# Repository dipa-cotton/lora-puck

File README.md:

# lora-puck
LoRA!!
## pictures

## project overview
A long range radio system with lots of features! it integrates boards with sensors and reads the data with an esp32, and communicates using an SX1262, on ham radio frequencies so i can pick them up from far far away :DD along with a 0.96 inch OLED display, a microSD card module, and more, this project is versatile and can do much more than your average tiny radio!
## pictures
There was no CAD Case built because this is going to be put in a solar powered plane built by an organization that I don't have the dimentions for yet. I will update the CAD as soon as I receive those dimentions!
### Overall Cost: $72
see BOM.csv for more specifics!

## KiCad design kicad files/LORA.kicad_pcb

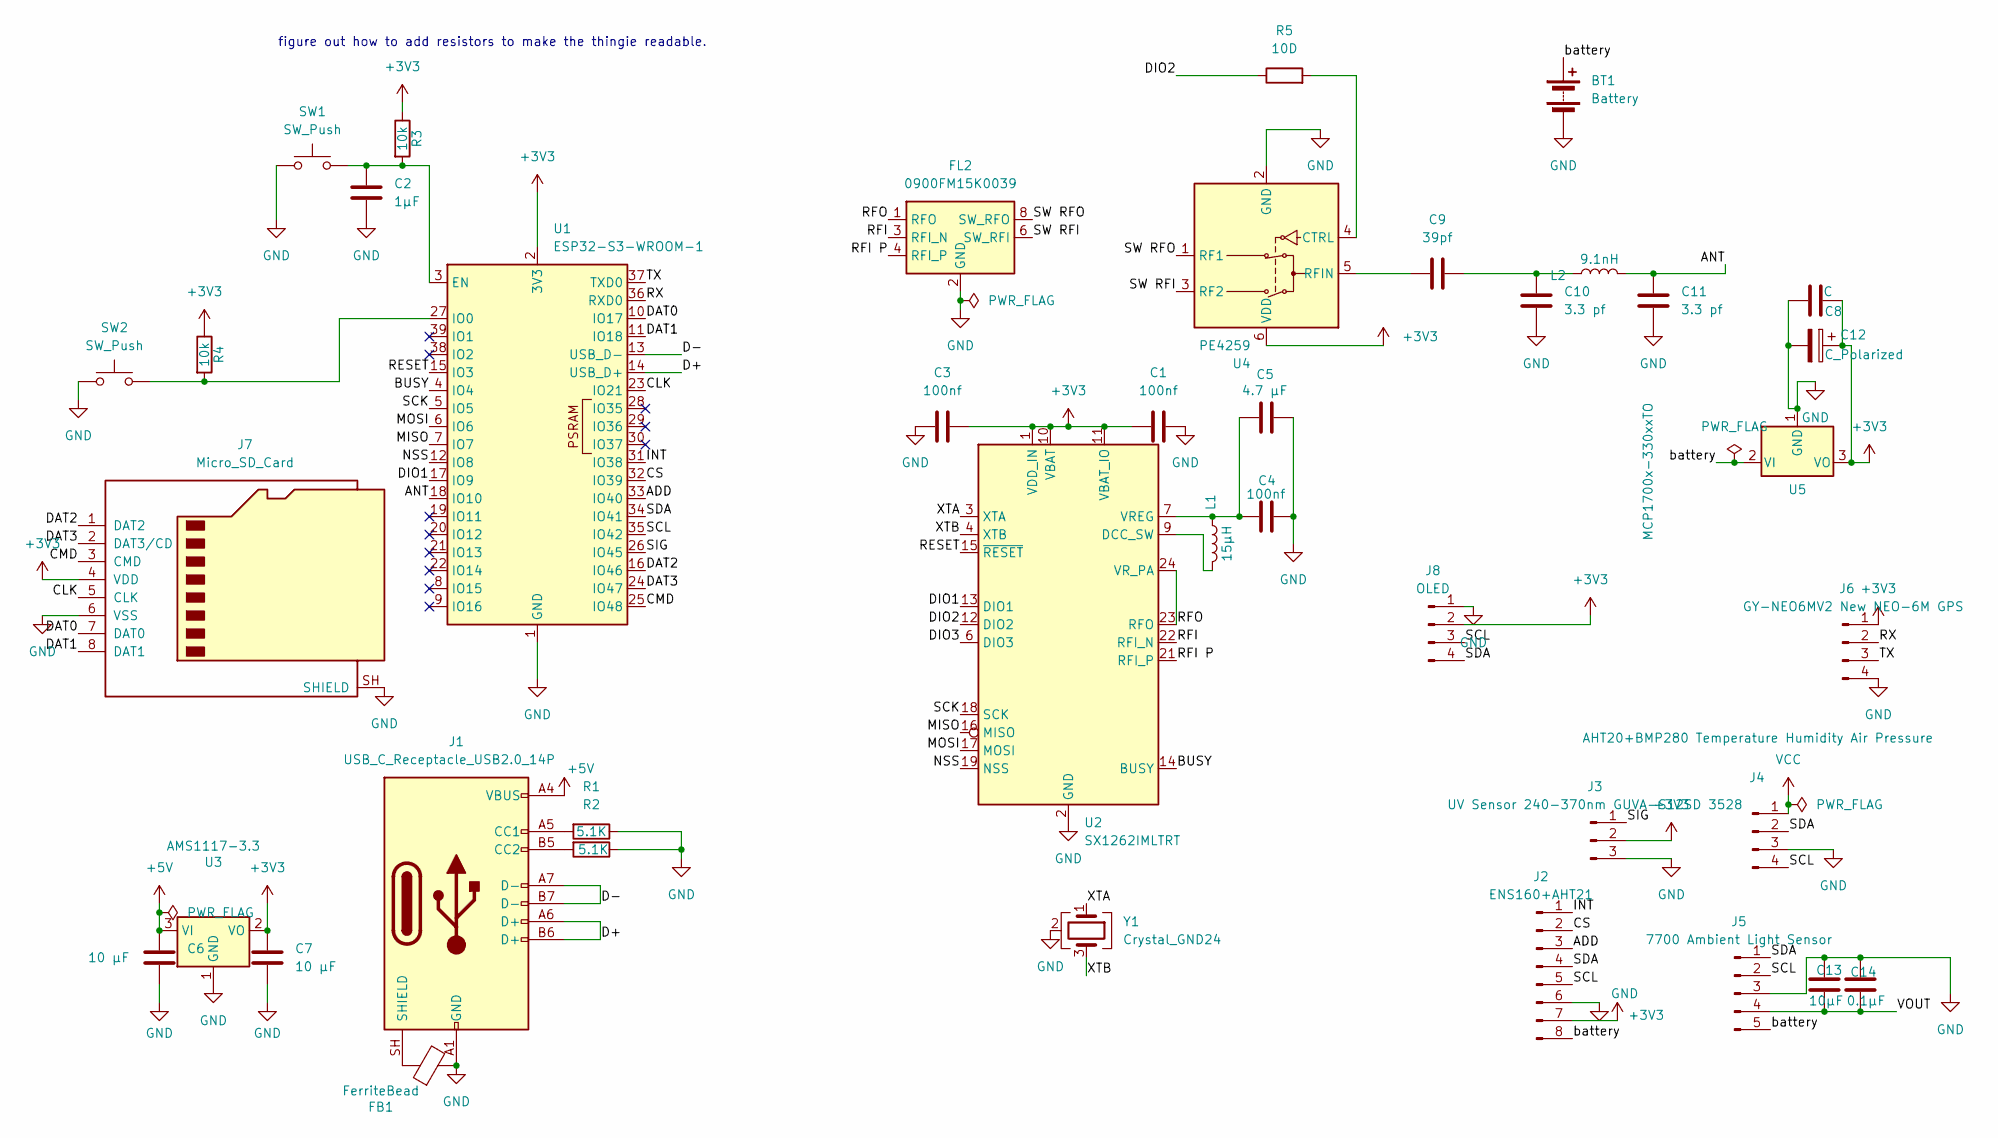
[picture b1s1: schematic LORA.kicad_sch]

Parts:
BT1: Battery; BatteryHolder_Keystone_2462_2xAA
C1, C3, C4: 100nf; C_0402_1005Metric_Pad0.74x0.62mm_HandSolder
C2: 1µF; R_0603_1608Metric
C5: 4.7 µF; C_0402_1005Metric_Pad0.74x0.62mm_HandSolder
C6, C7: 10 µF; C_0402_1005Metric_Pad0.74x0.62mm_HandSolder
C8: C; R_0603_1608Metric
C9: 39pf; R_0603_1608Metric
C10, C11: 3.3 pf; R_0603_1608Metric
C12: C_Polarized; C_Radial_D6.3mm_H7.0mm_P2.50mm
C13: 10µF; R_0603_1608Metric
C14: 0.1µF; R_0603_1608Metric
FB1: FerriteBead; LairdTech_28C0236-0JW-10
FL2: 0900FM15K0039; Balun_Johanson_0900FM15K0039
J1: USB_C_Receptacle_USB2.0_14P; USB_C_Receptacle_GCT_USB4085
J2: ENS160+AHT21; PinHeader_1x08_P2.54mm_Vertical
J3: UV Sensor 240-370nm GUVA-S12SD 3528; PinHeader_1x03_P2.54mm_Vertical
J4: AHT20+BMP280 Temperature Humidity Air Pressure; PinHeader_1x04_P2.54mm_Vertical
J5: 7700 Ambient Light Sensor; PinHeader_1x05_P2.54mm_Vertical
J6: GY-NEO6MV2 New NEO-6M GPS; PinHeader_1x04_P2.54mm_Vertical
J7: Micro_SD_Card; microSD_HC_Wuerth_693072010801
J8: OLED; PinHeader_1x04_P2.54mm_Vertical
L1: 15µH; R_0402_1005Metric_Pad0.72x0.64mm_HandSolder
L2: 9.1nH; R_0402_1005Metric_Pad0.72x0.64mm_HandSolder
R1, R2: 5.1K; R_0402_1005Metric_Pad0.72x0.64mm_HandSolder
R3, R4: 10k; R_0402_1005Metric_Pad0.72x0.64mm_HandSolder
R5: 10D; R_0603_1608Metric
SW1, SW2: SW_Push; SW_Push_1P1T_NO_CK_PTS125Sx43SMTR
U1: ESP32-S3-WROOM-1
U2: SX1262IMLTRT; QFN-24-1EP_4x4mm_P0.5mm_EP2.6x2.6mm
U3: AMS1117-3.3; SOT-223-3_TabPin2
U4: PE4259; SOT-363_SC-70-6
U5: MCP1700x-330xxTO; TO-92_Inline
Y1: Crystal_GND24; Crystal_DS10_D1.0mm_L4.3mm_Horizontal_1EP_style1

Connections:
+3V3: C1.1, C3.2, C7.1, C8.1, C12.1, J2.7, J3.2, J6.1, J7.4 (VDD), J8.2, R3.1, R4.1, U1.2 (3V3), U2.1 (VDD_IN), U2.10 (VBAT), U2.11 (VBAT_IO), U3.2 (VO), U4.6 (VDD), U5.3 (VO)
+5V: C6.1, J1.A4 (VBUS), J1.A9 (VBUS), J1.B4 (VBUS), J1.B9 (VBUS), U3.3 (VI)
/ADD: J2.3, U1.33 (IO40)
/ANT: C11.2, L2.2, U1.18 (IO10)
/BUSY: U1.4 (IO4), U2.14 (BUSY)
/CLK: J7.5 (CLK), U1.23 (IO21)
/CMD: J7.3 (CMD), U1.25 (IO48)
/CS: J2.2, U1.32 (IO39)
/D+: J1.A6 (D+), J1.B6 (D+), U1.14 (USB_D+)
/D-: J1.A7 (D-), J1.B7 (D-), U1.13 (USB_D-)
/DAT0: J7.7 (DAT0), U1.10 (IO17)
/DAT1: J7.8 (DAT1), U1.11 (IO18)
/DAT2: J7.1 (DAT2), U1.16 (IO46)
/DAT3: J7.2 (DAT3/CD), U1.24 (IO47)
/DIO1: U1.17 (IO9), U2.13 (DIO1)
/DIO2: R5.1, U2.12 (DIO2)
/DIO3: U2.6 (DIO3)
/INT: J2.1, U1.31 (IO38)
/MISO: U1.7 (IO7), U2.16 (MISO)
/MOSI: U1.6 (IO6), U2.17 (MOSI)
/NSS: U1.12 (IO8), U2.19 (NSS)
/RESET: U1.15 (IO3), U2.15 (~RESET)
/RFI: FL2.3 (RFI_N), U2.22 (RFI_N)
/RFI P: FL2.4 (RFI_P), U2.21 (RFI_P)
/RFO: FL2.1 (RFO), U2.23 (RFO), U2.24 (VR_PA)
/RX: J6.2, U1.36 (RXD0)
/SCK: U1.5 (IO5), U2.18 (SCK)
/SCL: J2.5, J4.4, J5.2, J8.3, U1.35 (IO42)
/SDA: J2.4, J4.2, J5.1, J8.4, U1.34 (IO41)
/SIG: J3.1, U1.26 (IO45)
/SW RFI: FL2.6 (SW_RFI), U4.3 (RF2)
/SW RFO: FL2.8 (SW_RFO), U4.1 (RF1)
/TX: J6.3, U1.37 (TXD0)
/VOUT: C13.2, C14.2, J5.4
/XTA: U2.3 (XTA), Y1.1
/XTB: U2.4 (XTB), Y1.3
/battery: BT1.1 (+), J2.8, J5.5, U5.2 (VI)
GND: BT1.2 (-), C1.2, C2.2, C3.1, C4.2, C5.2, C6.2, C7.2, C8.2, C10.1, C11.1, C12.2, C13.1, C14.1, FB1.2, FL2.2 (GND), FL2.5 (GND), FL2.7 (GND), FL2.9 (GND), FL2.10 (GND), J1.A1 (GND), J1.A12 (GND), J1.B1 (GND), J1.B12 (GND), J2.6, J3.3, J4.3, J5.3, J6.4, J7.6 (VSS), J7.SH (SHIELD), J8.1, R1.1, R2.1, SW1.1, SW2.1, U1.1 (GND), U1.40 (GND), U1.41 (GND), U2.2 (GND), U2.5 (GND), U2.8 (GND), U2.20 (GND), U2.25 (GND), U3.1 (GND), U4.2 (GND), U5.1 (GND), Y1.2 (G), Y1.4 (G)
unnamed: C9.1, C10.2, L2.1
unnamed: J1.A5 (CC1), R1.2
unnamed: J1.B5 (CC2), R2.2
unnamed: FB1.1, J1.SH (SHIELD)
unnamed: C2.1, R3.2, SW1.2, U1.3 (EN)
unnamed: R4.2, SW2.2, U1.27 (IO0)
unnamed: L1.2, U2.9 (DCC_SW)
unnamed: C4.1, C5.1, L1.1, U2.7 (VREG)
unnamed: R5.2, U4.4 (CTRL)
unnamed: C9.2, U4.5 (RFIN)
VCC: J4.1

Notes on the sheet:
figure out how to add resistors to make the thingie readable.

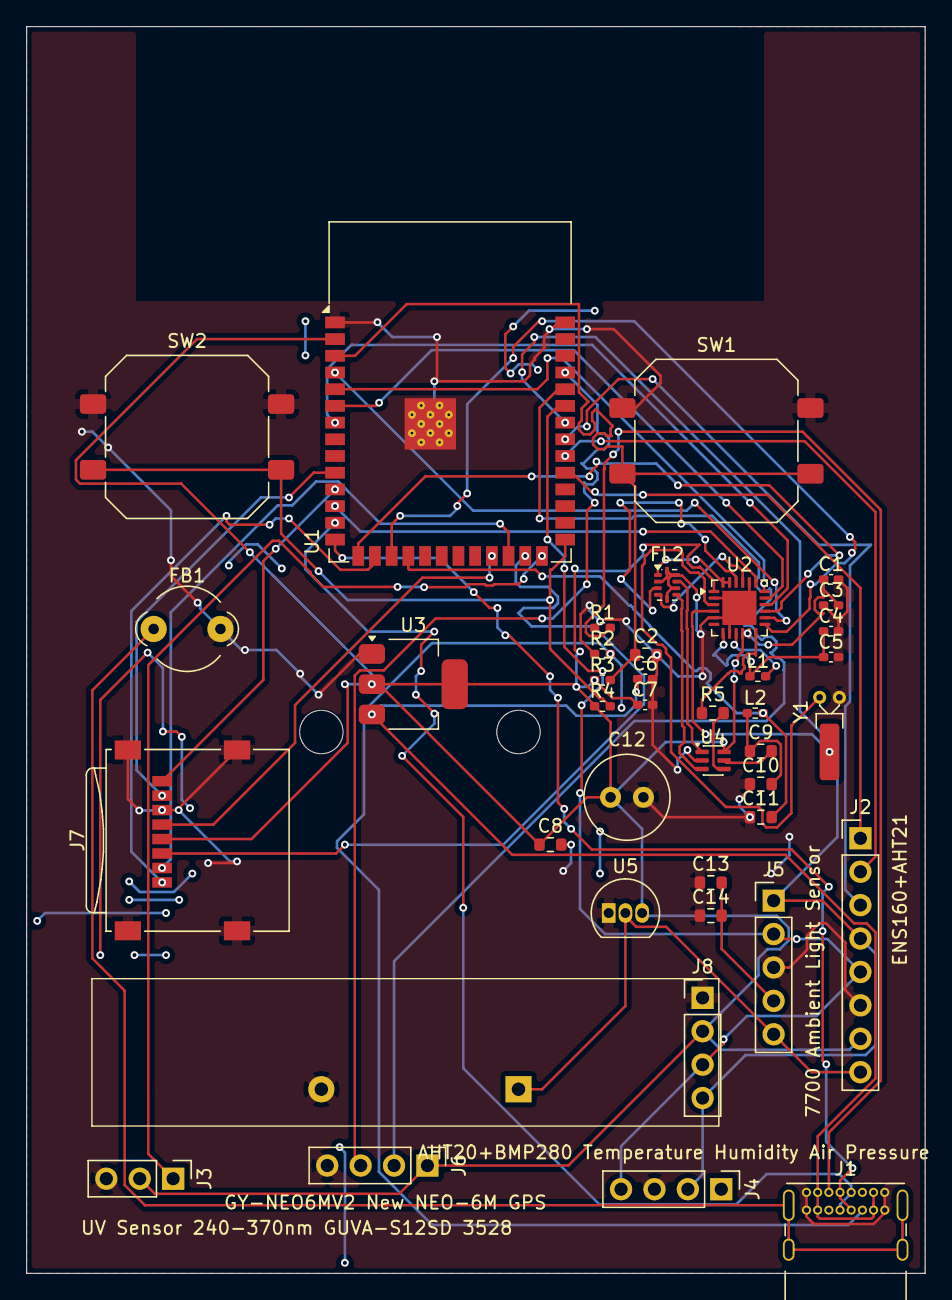
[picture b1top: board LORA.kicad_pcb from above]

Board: 2 copper layers, 68.3 x 94.8 mm, 40 parts (1 on the bottom side), 47 nets.

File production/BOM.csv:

Reference,Qty,Value,Cost,Link,Footprint,,Datasheet
BT1,1,Battery,0.5,https://www.aliexpress.us/item/3256807960114360.html?spm=a2g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,Battery:BatteryHolder_Keystone_2462_2xAA,,
"SW1,SW2",2,SW_Push,Owned,,Button_Switch_SMD:SW_Push_1P1T_NO_CK_PTS125Sx43SMTR,,
"C1,C3,C4",3,100nf,4,https://www.aliexpress.com/ssr/300000512/BundleDeals2?spm=a2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,Capacitor_SMD:C_0402_1005Metric_Pad0.74x0.62mm_HandSolder,,
C5,1,4.7 µF,included in kit,,Capacitor_SMD:C_0402_1005Metric_Pad0.74x0.62mm_HandSolder,,
"C6,C7",2,10 µF,included in kit,,Capacitor_SMD:C_0402_1005Metric_Pad0.74x0.62mm_HandSolder,,
C12,1,C_Polarized,Owned,,Capacitor_THT:C_Radial_D6.3mm_H7.0mm_P2.50mm,,
J7,1,Micro_SD_Card,3.5,https://www.mouser.com/en/ProductDetail/Wurth-Elektronik/693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,Connector_Card:microSD_HC_Wuerth_693072010801,,https://www.we-online.com/components/products/datasheet/6930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
J3,1,UV Sensor 240-370nm GUVA-S12SD 3528,3,https://www.aliexpress.us/item/3256806094286151.html,Connector_PinHeader_2.54mm:PinHeader_1x03_P2.54mm_Vertical,,
J4,1,AHT20+BMP280 Temperature Humidity Air Pressure,3,https://www.aliexpress.us/item/3256807516159141.html ,Connector_PinHeader_2.54mm:PinHeader_1x04_P2.54mm_Vertical,,
J6,1,GY-NEO6MV2 New NEO-6M GPS,3,https://www.aliexpress.us/item/3256807316352883.html ,Connector_PinHeader_2.54mm:PinHeader_1x04_P2.54mm_Vertical,,
J8,1,OLED,3,https://www.aliexpress.us/item/3256812792834091.html,Connector_PinHeader_2.54mm:PinHeader_1x04_P2.54mm_Vertical,,
J5,1,7700 Ambient Light Sensor,3,https://www.aliexpress.us/item/3256810505327028.html,Connector_PinHeader_2.54mm:PinHeader_1x05_P2.54mm_Vertical,,
J2,1,ENS160+AHT21,3,https://www.aliexpress.us/item/3256808312530292.html ,Connector_PinHeader_2.54mm:PinHeader_1x08_P2.54mm_Vertical,,
J1,1,USB_C_Receptacle_USB2.0_14P,1,https://www.digikey.com/en/products/detail/gct/USB4085-GF-A/9859662,Connector_USB:USB_C_Receptacle_GCT_USB4085,,https://www.usb.org/sites/default/files/documents/usb_type-c.zip
Y1,1,Crystal_GND24,0.5,https://www.mouser.com/en/ProductDetail/Murata-Electronics/C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,Crystal:Crystal_DS10_D1.0mm_L4.3mm_Horizontal_1EP_style1,,
FB1,1,FerriteBead,1.1,https://www.digikey.com/en/products/detail/laird-signal-inte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,Ferrite_THT:LairdTech_28C0236-0JW-10,,
U2,1,SX1262IMLTRT,9,https://www.digikey.com/en/products/detail/semtech-corporati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,Package_DFN_QFN:QFN-24-1EP_4x4mm_P0.5mm_EP2.6x2.6mm,,https://semtech.file.force.com/sfc/dist/version/download/?oi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
U3,1,AMS1117-3.3,0.5,https://www.digikey.com/en/products/detail/umw/AMS1117-3-3/17635254,Package_TO_SOT_SMD:SOT-223-3_TabPin2,,http://www.advanced-monolithic.com/pdf/ds1117.pdf
U4,1,PE4259,1,https://www.digikey.com/en/products/detail/psemi/4259-63/2614473,Package_TO_SOT_SMD:SOT-363_SC-70-6,,https://lcsc.com/datasheet/lcsc_datasheet_2409301504_pSemi-P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
U5,1,MCP1700x-330xxTO,0.5,https://www.digikey.com/en/products/detail/microchip-technol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,Package_TO_SOT_THT:TO-92_Inline,,http://ww1.microchip.com/downloads/en/DeviceDoc/20001826D.pdf
L1,1,15µH,1,https://www.digikey.com/en/products/detail/bourns-inc/RL622-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,Resistor_SMD:R_0402_1005Metric_Pad0.72x0.64mm_HandSolder,,
L2,1,9.1nH,0.5,https://www.digikey.com/en/products/detail/murata-electronic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,Resistor_SMD:R_0402_1005Metric_Pad0.72x0.64mm_HandSolder,,
"R1,R2",2,5.1K,4,https://www.aliexpress.com/ssr/300000512/BundleDeals2?spm=a2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,Resistor_SMD:R_0402_1005Metric_Pad0.72x0.64mm_HandSolder,,
"R3,R4",2,10k,included in kit,,Resistor_SMD:R_0402_1005Metric_Pad0.72x0.64mm_HandSolder,,
C2,1,1µF,included in kit,,Resistor_SMD:R_0603_1608Metric,,
C8,1,C,included in kit,,Resistor_SMD:R_0603_1608Metric,,
C9,1,39pf,included in kit,,Resistor_SMD:R_0603_1608Metric,,
"C10,C11",2,3.3 pf,included in kit,,Resistor_SMD:R_0603_1608Metric,,
C13,1,10µF,included in kit,,Resistor_SMD:R_0603_1608Metric,,
C14,1,0.1µF,included in kit,,Resistor_SMD:R_0603_1608Metric,,
R5,1,10D,included in kit,,Resistor_SMD:R_0603_1608Metric,,
FL2,1,0900FM15K0039,0.5,https://www.digikey.com/en/products/detail/johanson-technolo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,RF_Converter:Balun_Johanson_0900FM15K0039,,https://www.johansontechnology.com/datasheets/0900FM15K0039/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
U1,1,ESP32-S3-WROOM-1,7,https://www.digikey.com/en/products/detail/espressif-systems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,RF_Module:ESP32-S3-WROOM-1,,https://www.espressif.com/sites/default/files/documentation/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
,,,52.1,,,,
,,shipping,10,5,7,,
,,total,74.1,,,,
